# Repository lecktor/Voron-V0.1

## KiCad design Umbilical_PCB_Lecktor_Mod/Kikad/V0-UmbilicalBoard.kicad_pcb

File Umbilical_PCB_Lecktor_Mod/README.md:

# Umbilical PCB by T.Abraham (Lecktor Mod)

## Changes:
+ Swapped pins on Neopixel IN connector to match controller
+ Added extra 5V connector for Neopixels to not overload skr 5v power line
+ Flipped Neopixel OUTS on top of PCB

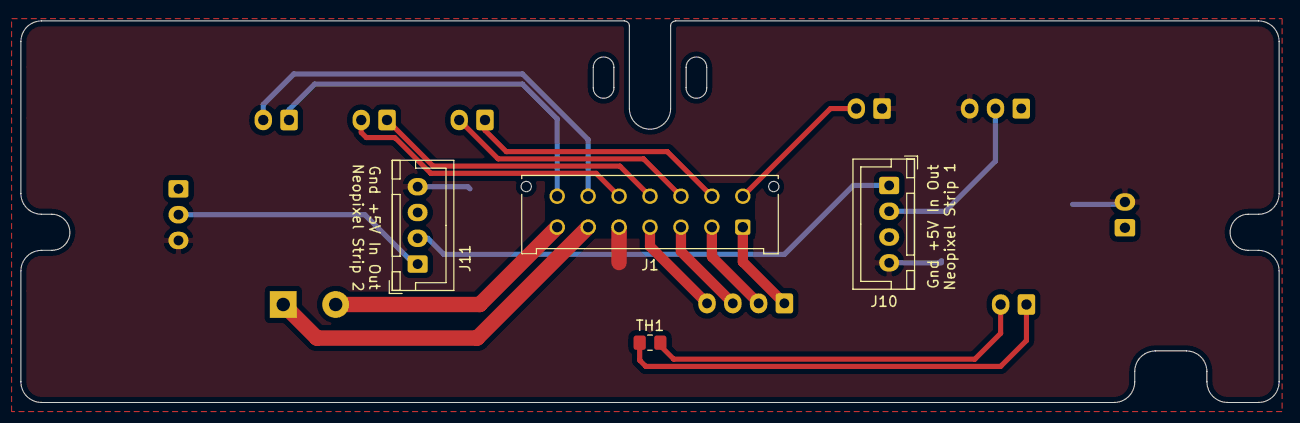
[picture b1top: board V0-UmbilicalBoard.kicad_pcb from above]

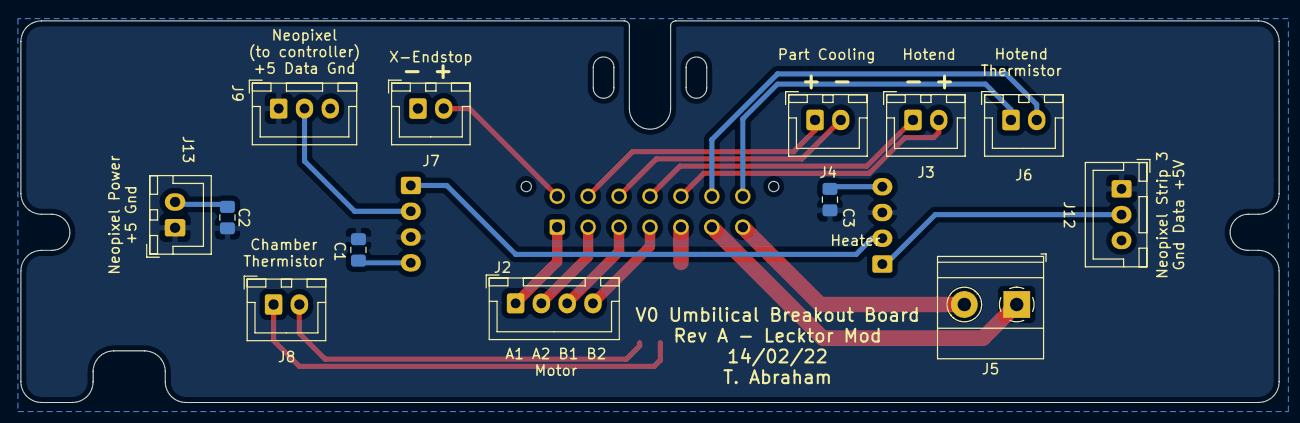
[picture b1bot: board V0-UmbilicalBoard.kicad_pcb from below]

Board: 2 copper layers, 122.0 x 37.0 mm, 17 parts (13 on the bottom side), 20 nets.

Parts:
C1, C2, C3: C; C_0805_2012Metric_Pad1.18x1.45mm_HandSolder
J1: Conn_02x08_Odd_Even; Molex_Micro-Fit_3.0_43045-1412_2x07_P3.00mm_Vertical
J2: Motor; JST_XH_B4B-XH-A_1x04_P2.50mm_Vertical
J3: Hotend Fan; JST_XH_B2B-XH-A_1x02_P2.50mm_Vertical
J4: Part Cooling Fan; JST_XH_B2B-XH-A_1x02_P2.50mm_Vertical
J5: Heater; TerminalBlock_Phoenix_MKDS-1,5-2-5.08_1x02_P5.08mm_Horizont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
J6: Thermistor; JST_XH_B2B-XH-A_1x02_P2.50mm_Vertical
J7: X-Endstop; JST_XH_B2B-XH-A_1x02_P2.50mm_Vertical
J8: Chamber Thermistor; JST_XH_B2B-XH-A_1x02_P2.50mm_Vertical
J9: Neopixel (from controller); JST_XH_B3B-XH-A_1x03_P2.50mm_Vertical
J10, J11: Neopixel Strip 1; JST_XH_B4B-XH-A_1x04_P2.50mm_Vertical
J12: Neopixel Out; JST_XH_B3B-XH-A_1x03_P2.50mm_Vertical
J13: Neopixel 5V Power; JST_XH_B2B-XH-A_1x02_P2.50mm_Vertical
TH1: Thermistor; R_0805_2012Metric_Pad1.20x1.40mm_HandSolder

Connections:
5V: C1.1, C2.1, C3.1, J9.1, J10.3, J11.3, J12.1, J13.1
/A1: J1.1, J2.1
/A2: J1.2, J2.2
/B1: J1.3, J2.3
/B2: J1.4, J2.4
/Hotend_Fan+: J1.12, J3.2
/Hotend_Fan-: J1.11, J3.1
/PartFan+: J1.9, J4.1
/PartFan-: J1.10, J4.2
Data: J9.2, J10.2
DataIn2: J10.1, J11.2
DataOut2: J11.1, J12.2
Ground: C1.2, C2.2, C3.2, J1.5, J7.1, J9.3, J10.4, J11.4, J12.3, J13.2
unnamed: J1.6, J5.1
unnamed: J1.7, J5.2
unnamed: J1.8, J7.2
unnamed: J1.13, J6.2
unnamed: J1.14, J6.1
unnamed: J8.1, TH1.1
unnamed: J8.2, TH1.2

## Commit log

2022-01-14 ínitial folder structure
2022-01-14 Source files and readme
2022-01-14 added shop link
2022-01-19 Umbilical Toolhead Soldering Tool
2022-03-21 Added leds config
2022-03-24 leds configuration instructions
2022-03-24 link
2022-04-15 pcb files upload
